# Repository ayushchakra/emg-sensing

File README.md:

# EMG Sensing Circuit Board

Electromygraphy is a medical tool used to evaluate the health of individual muscles and
the nerve cells that dictate their movement. The intention of this project was to design a
four-channel surface electromygraphy (sEMG) printed circuit board in order to process
real-time electromyographic signals generated from a user’s muscle movements. The
board was intended to communicate with a user’s computer via Bluetooth and Serial
to provide flexibility to the physical setup, along with portability for ease of access to
EMG information. The full hardware and software overview can be found [here](https://github.com/ayushchakra/emg-sensing/blob/main/EMG_sensing_final.pdf).

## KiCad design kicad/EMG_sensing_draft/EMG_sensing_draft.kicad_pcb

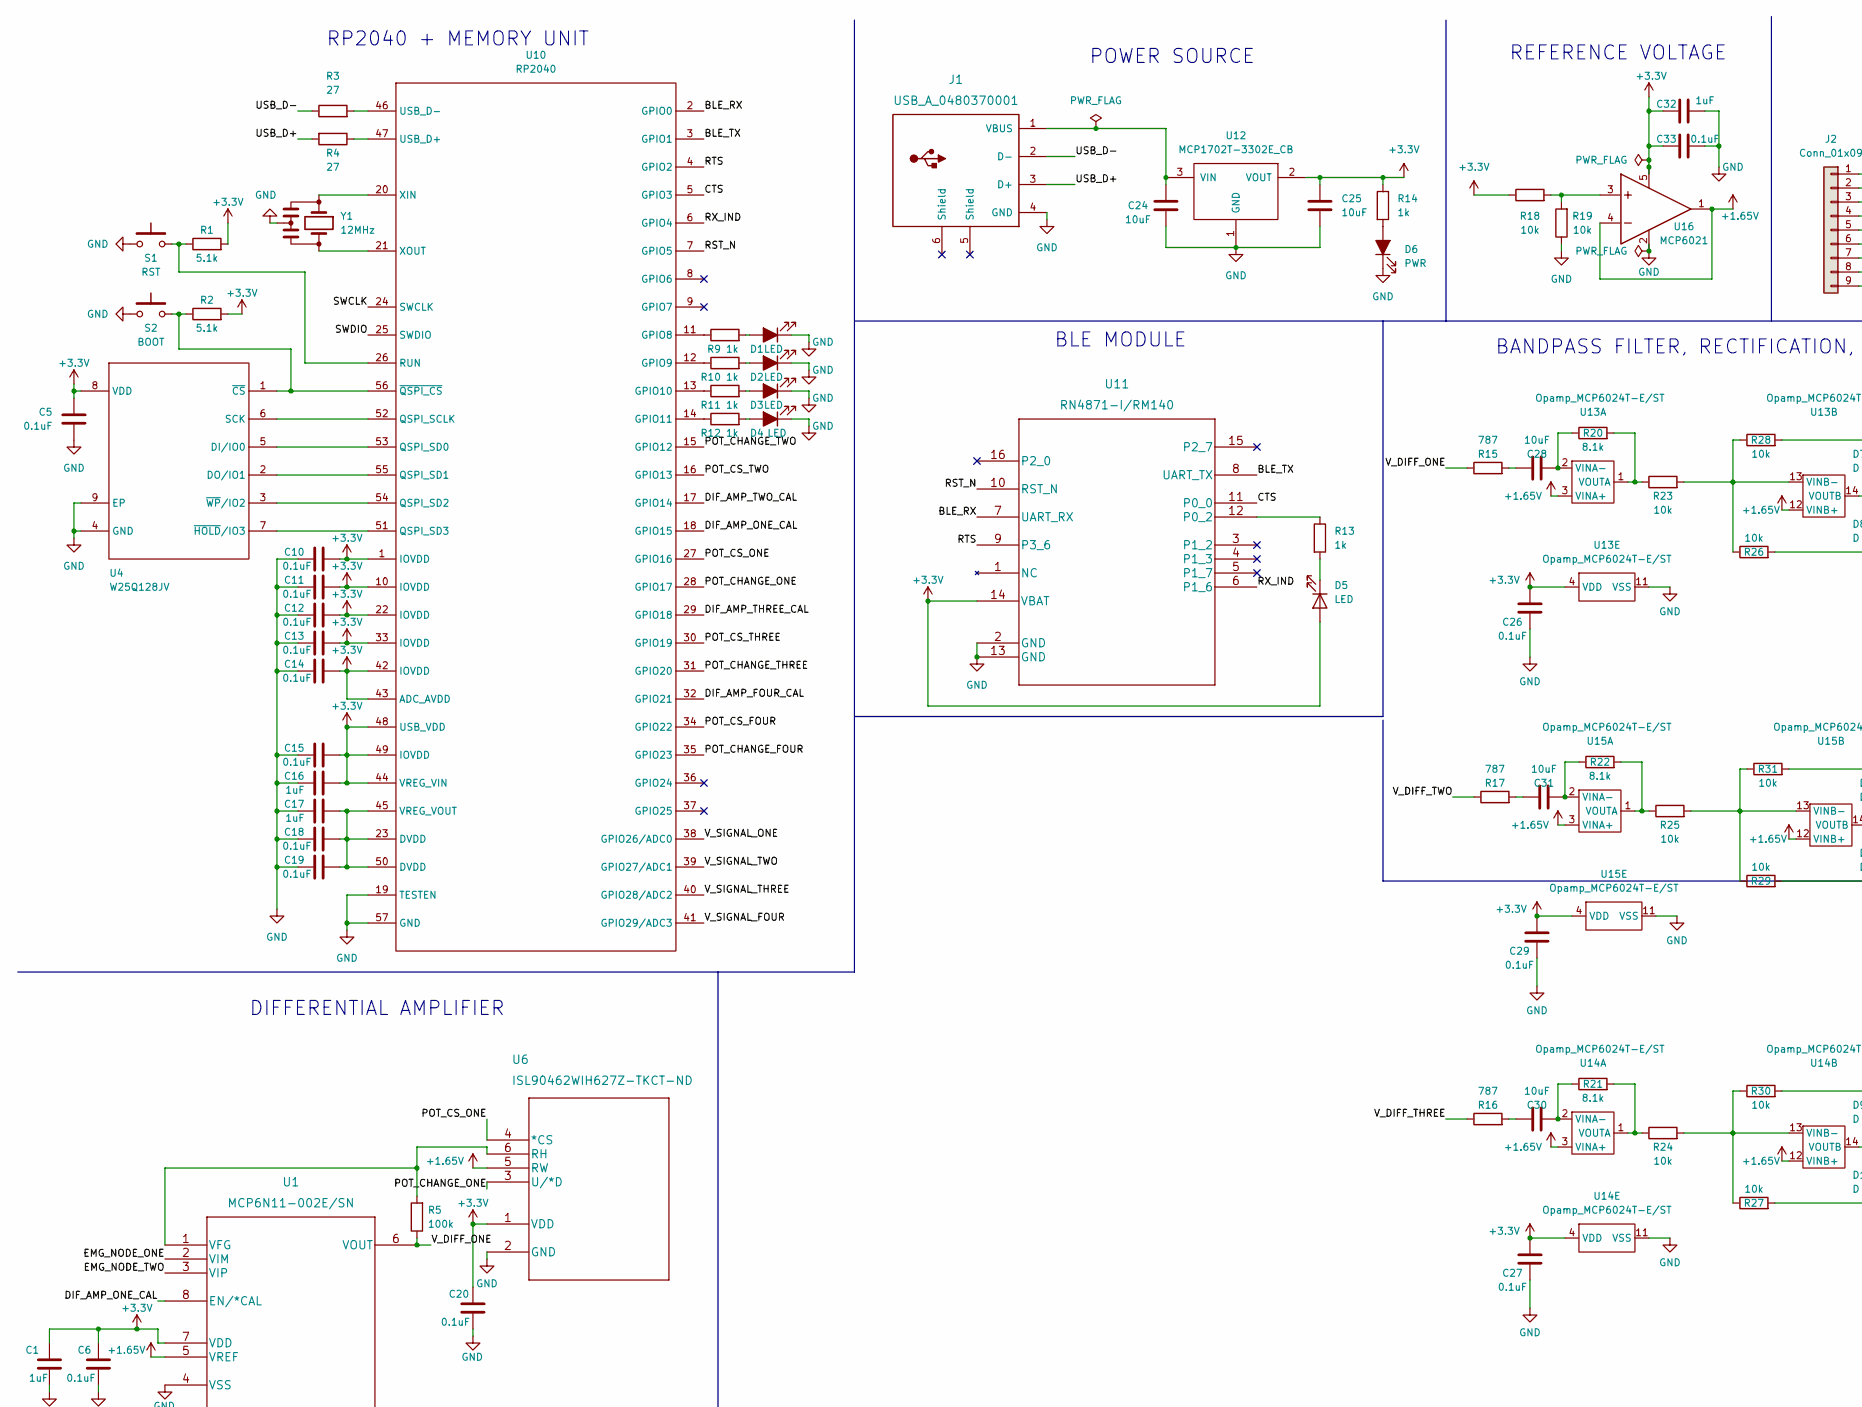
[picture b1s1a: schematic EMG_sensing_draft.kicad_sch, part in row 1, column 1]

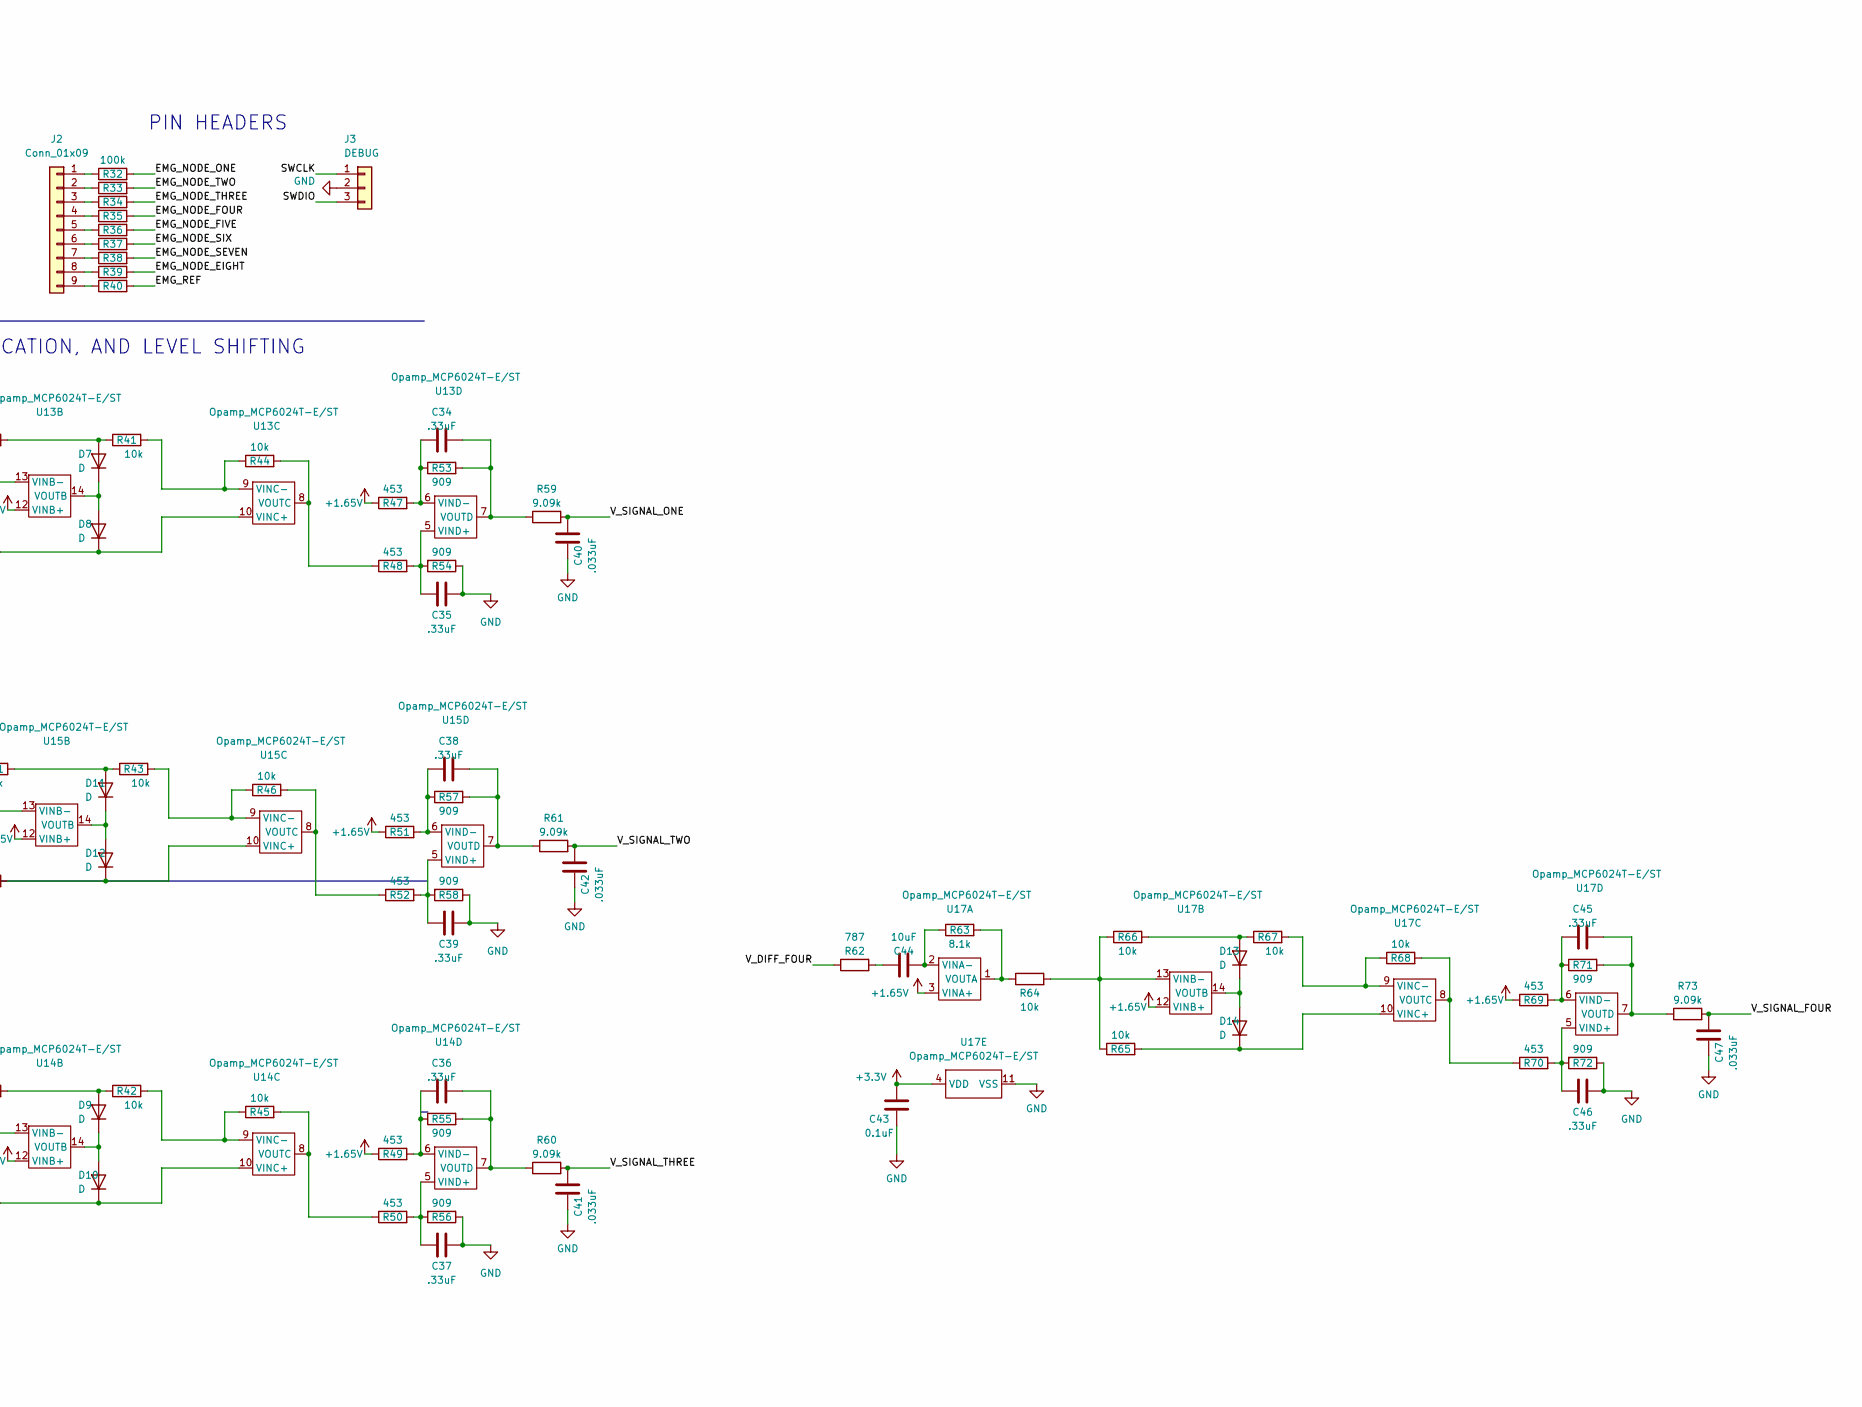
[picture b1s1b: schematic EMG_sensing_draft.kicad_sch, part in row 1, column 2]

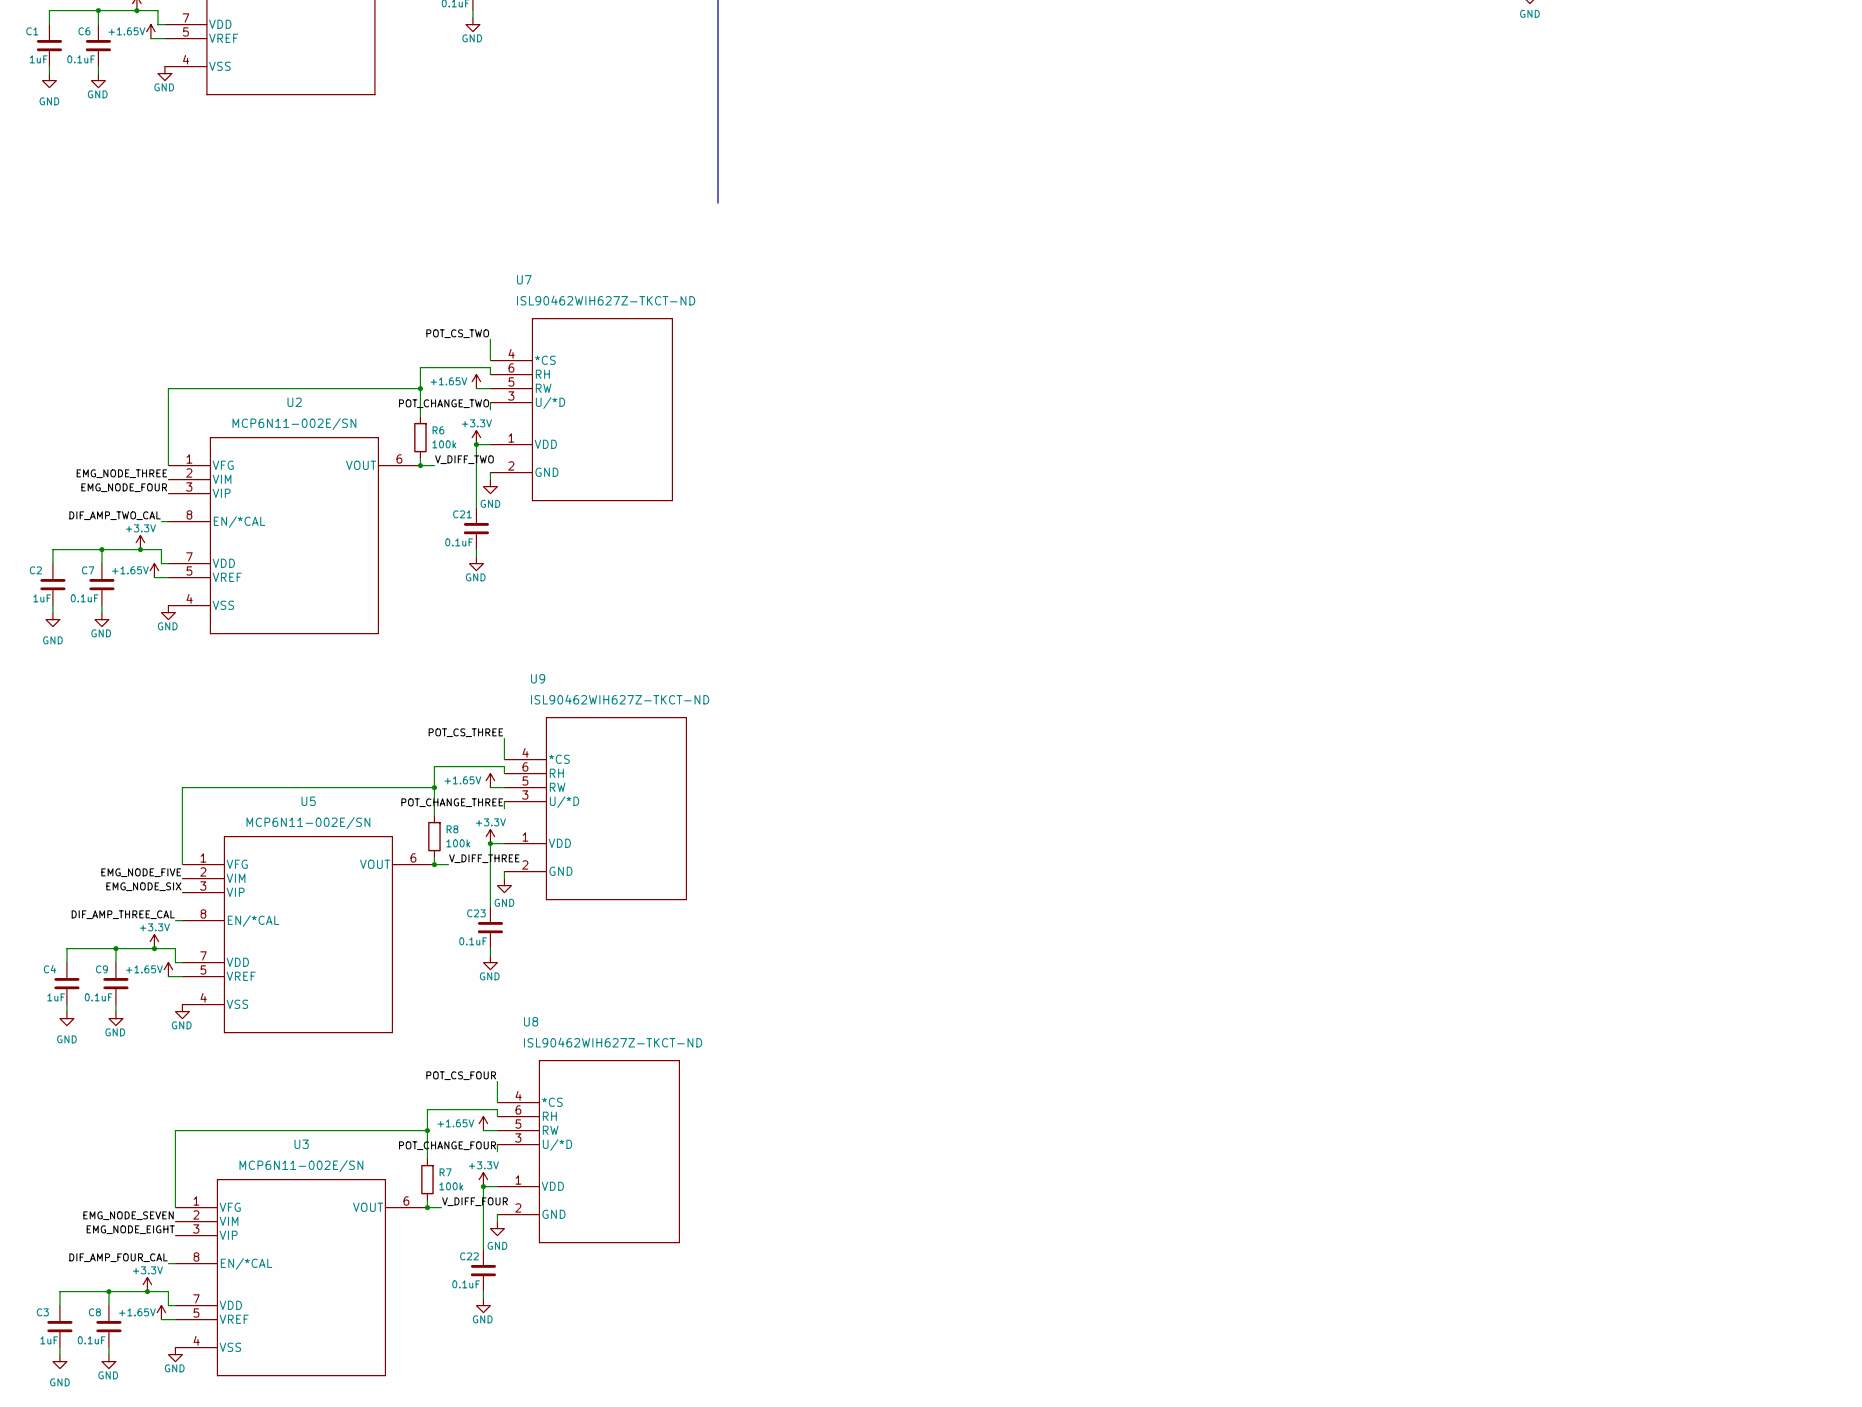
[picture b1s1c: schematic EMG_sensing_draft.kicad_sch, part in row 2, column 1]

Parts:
C1, C2, C3, C4, C16, C17, C32: 1uF; C_0603_1608Metric
C5, C6, C7, C8, C9, C10, C11, C12, C13, C14, C15, C18, C19, C20, C21, C22, C23, C26, C27, C29, C33, C43: 0.1uF; C_0603_1608Metric
C24, C25, C28, C30, C31, C44: 10uF; C_0603_1608Metric
C34, C35, C36, C37, C38, C39, C45, C46: .33uF; C_0603_1608Metric
C40, C41, C42, C47: .033uF; C_0603_1608Metric
D1, D2, D3, D4, D5: LED; LED_0805_2012Metric
D6: PWR; LED_0805_2012Metric
D7, D8, D9, D10, D11, D12, D13, D14: D; D_0805_2012Metric
J1: USB_A_0480370001
J2: Conn_01x09; PinSocket_1x09_P2.54mm_Vertical
J3: DEBUG; PinHeader_1x03_P2.54mm_Vertical
R1, R2: 5.1k; R_0603_1608Metric
R3, R4: 27; R_0603_1608Metric
R5, R6, R7, R8, R32, R33, R34, R35, R36, R37, R38, R39, R40: 100k; R_0603_1608Metric
R9, R10, R11, R12, R13, R14: 1k; R_0603_1608Metric
R15, R16, R17, R62: 787; R_0603_1608Metric
R18, R19, R23, R24, R25, R26, R27, R28, R29, R30, R31, R41, R42, R43, R44, R45, R46, R64, R65, R66, R67, R68: 10k; R_0603_1608Metric
R20, R21, R22, R63: 8.1k; R_0603_1608Metric
R47, R48, R49, R50, R51, R52, R69, R70: 453; R_0603_1608Metric
R53, R54, R55, R56, R57, R58, R71, R72: 909; R_0603_1608Metric
R59, R60, R61, R73: 9.09k; R_0603_1608Metric
S1: RST; TL3301AFxxxxJ
S2: BOOT; TL3301AFxxxxJ
U1, U2, U3, U5: MCP6N11-002E/SN; MCP6N11-002ESN
U4: W25Q128JV; WSON-8-1EP_6x5mm_P1.27mm_EP3.4x4.3mm
U6, U7, U8, U9: ISL90462WIH627Z-TKCT-ND
U10: RP2040
U11: RN4871-I/RM140; RN4871
U12: MCP1702T-3302E_CB; SOT-23
U13, U14, U15, U17: Opamp_MCP6024T-E/ST; MCP6024T
U16: MCP6021; SOT-23-5
Y1: 12MHz; CSTNE

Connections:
+1.65V: R47.1, R49.1, R51.1, R69.1, U1.5 (VREF), U2.5 (VREF), U3.5 (VREF), U5.5 (VREF), U6.5 (RW), U7.5 (RW), U8.5 (RW), U9.5 (RW), U13.3 (VINA+), U13.12 (VINB+), U14.3 (VINA+), U14.12 (VINB+), U15.3 (VINA+), U15.12 (VINB+), U16.1, U16.4, U17.3 (VINA+), U17.12 (VINB+)
+3.3V: C1.1, C2.1, C3.1, C4.1, C5.2, C6.1, C7.1, C8.1, C9.1, C10.1, C11.1, C12.1, C13.1, C14.1, C15.1, C16.1, C20.1, C21.1, C22.1, C23.1, C25.1, C26.2, C27.2, C29.2, C32.1, C33.1, C43.2, D5.2 (A), R1.2, R2.2, R14.1, R18.1, U1.7 (VDD), U2.7 (VDD), U3.7 (VDD), U4.8 (VDD), U5.7 (VDD), U6.1 (VDD), U7.1 (VDD), U8.1 (VDD), U9.1 (VDD), U10.1 (IOVDD), U10.10 (IOVDD), U10.22 (IOVDD), U10.33 (IOVDD), U10.42 (IOVDD), U10.43 (ADC_AVDD), U10.44 (VREG_VIN), U10.48 (USB_VDD), U10.49 (IOVDD), U11.14 (VBAT), U12.2 (VOUT), U13.4 (VDD), U14.4 (VDD), U15.4 (VDD), U16.5, U17.4 (VDD)
/BLE_RX: U10.2 (GPIO0), U11.7 (UART_RX)
/BLE_TX: U10.3 (GPIO1), U11.8 (UART_TX)
/CTS: U10.5 (GPIO3), U11.11 (P0_0)
/DIF_AMP_ONE_CAL: U1.8 (EN/*CAL), U10.18 (GPIO15)
/DIF_AMP_THREE_CAL: U5.8 (EN/*CAL), U10.29 (GPIO18)
/DIF_AMP_TWO_CAL: U2.8 (EN/*CAL), U10.17 (GPIO14)
/EMG_NODE_EIGHT: R39.2, U3.3 (VIP)
/EMG_NODE_FIVE: R36.2, U5.2 (VIM)
/EMG_NODE_FOUR: R35.2, U2.3 (VIP)
/EMG_NODE_ONE: R32.2, U1.2 (VIM)
/EMG_NODE_SEVEN: R38.2, U3.2 (VIM)
/EMG_NODE_SIX: R37.2, U5.3 (VIP)
/EMG_NODE_THREE: R34.2, U2.2 (VIM)
/EMG_NODE_TWO: R33.2, U1.3 (VIP)
/EMG_REF: R40.2
/POT_CHANGE_ONE: U6.3 (U/*D), U10.28 (GPIO17)
/POT_CHANGE_THREE: U9.3 (U/*D), U10.31 (GPIO20)
/POT_CHANGE_TWO: U7.3 (U/*D), U10.15 (GPIO12)
/POT_CS_FOUR: U8.4 (*CS), U10.34 (GPIO22), U10.36 (GPIO24)
/POT_CS_ONE: U6.4 (*CS), U10.27 (GPIO16)
/POT_CS_THREE: U9.4 (*CS), U10.30 (GPIO19)
/POT_CS_TWO: U7.4 (*CS), U10.16 (GPIO13)
/RST_N: U10.7 (GPIO5), U11.10 (RST_N)
/RTS: U10.4 (GPIO2), U11.9 (P3_6)
/RX_IND: U10.6 (GPIO4), U11.6 (P1_6)
/SWCLK: J3.1, U10.24 (SWCLK)
/SWDIO: J3.3, U10.25 (SWDIO)
/USB_D+: J1.3 (D+), R4.2
/USB_D-: J1.2 (D-), R3.1
/V_DIFF_FOUR: R7.1, R62.1, U3.6 (VOUT)
/V_DIFF_ONE: R5.1, R15.1, U1.6 (VOUT)
/V_DIFF_THREE: R8.1, R16.1, U5.6 (VOUT)
/V_DIFF_TWO: R6.1, R17.1, U2.6 (VOUT)
/V_SIGNAL_FOUR: C47.1, R73.2, U10.41 (GPIO29/ADC3)
/V_SIGNAL_ONE: C40.1, R59.2, U10.38 (GPIO26/ADC0)
/V_SIGNAL_THREE: C41.1, R60.2, U10.40 (GPIO28/ADC2)
/V_SIGNAL_TWO: C42.1, R61.2, U10.39 (GPIO27/ADC1)
GND: C1.2, C2.2, C3.2, C4.2, C5.1, C6.2, C7.2, C8.2, C9.2, C10.2, C11.2, C12.2, C13.2, C14.2, C15.2, C16.2, C17.2, C18.2, C19.2, C20.2, C21.2, C22.2, C23.2, C24.1, C25.2, C26.1, C27.1, C29.1, C32.2, C33.2, C35.1, C37.1, C39.1, C40.2, C41.2, C42.2, C43.1, C46.1, C47.2, D1.1 (K), D2.1 (K), D3.1 (K), D4.1 (K), D6.1 (K), J1.4 (GND), J3.2, R19.1, R54.1, R56.1, R58.1, R72.1, S1.1, S2.1, U1.4 (VSS), U2.4 (VSS), U3.4 (VSS), U4.4 (GND), U4.9 (EP), U5.4 (VSS), U6.2 (GND), U7.2 (GND), U8.2 (GND), U9.2 (GND), U10.19 (TESTEN), U10.57 (GND), U11.2 (GND), U11.13 (GND), U12.1 (GND), U13.11 (VSS), U14.11 (VSS), U15.11 (VSS), U16.2, U17.11 (VSS), Y1.2
unnamed: C17.1, C18.1, C19.1, U10.23 (DVDD), U10.45 (VREG_VOUT), U10.50 (DVDD)
unnamed: C24.2, J1.1 (VBUS), U12.3 (VIN)
unnamed: C28.1, R15.2
unnamed: C28.2, R20.1, U13.2 (VINA-)
unnamed: C30.1, R16.2
unnamed: C30.2, R21.1, U14.2 (VINA-)
unnamed: C31.1, R17.2
unnamed: C31.2, R22.1, U15.2 (VINA-)
unnamed: C34.1, R47.2, R53.1, U13.6 (VIND-)
unnamed: C34.2, R53.2, R59.1, U13.7 (VOUTD)
unnamed: C35.2, R48.2, R54.2, U13.5 (VIND+)
unnamed: C36.1, R49.2, R55.1, U14.6 (VIND-)
unnamed: C36.2, R55.2, R60.1, U14.7 (VOUTD)
unnamed: C37.2, R50.2, R56.2, U14.5 (VIND+)
unnamed: C38.1, R51.2, R57.1, U15.6 (VIND-)
unnamed: C38.2, R57.2, R61.1, U15.7 (VOUTD)
unnamed: C39.2, R52.2, R58.2, U15.5 (VIND+)
unnamed: C44.1, R62.2
unnamed: C44.2, R63.1, U17.2 (VINA-)
unnamed: C45.1, R69.2, R71.1, U17.6 (VIND-)
unnamed: C45.2, R71.2, R73.1, U17.7 (VOUTD)
unnamed: C46.2, R70.2, R72.2, U17.5 (VIND+)
unnamed: D1.2 (A), R9.2
unnamed: D2.2 (A), R10.2
unnamed: D3.2 (A), R11.2
unnamed: D4.2 (A), R12.2
unnamed: D5.1 (K), R13.2
unnamed: D6.2 (A), R14.2
unnamed: D7.1 (K), D8.2 (A), U13.14 (VOUTB)
unnamed: D7.2 (A), R28.2, R41.1
unnamed: D8.1 (K), R26.2, U13.10 (VINC+)
unnamed: D9.2 (A), R30.2, R42.1
unnamed: D10.1 (K), R27.2, U14.10 (VINC+)
unnamed: D9.1 (K), D10.2 (A), U14.14 (VOUTB)
unnamed: D11.1 (K), D12.2 (A), U15.14 (VOUTB)
unnamed: D11.2 (A), R31.2, R43.1
unnamed: D12.1 (K), R29.2, U15.10 (VINC+)
unnamed: D13.1 (K), D14.2 (A), U17.14 (VOUTB)
unnamed: D13.2 (A), R66.2, R67.1
unnamed: D14.1 (K), R65.2, U17.10 (VINC+)
unnamed: J2.1, R32.1
unnamed: J2.2, R33.1
unnamed: J2.3, R34.1
unnamed: J2.4, R35.1
unnamed: J2.5, R36.1
unnamed: J2.6, R37.1
unnamed: J2.7, R38.1
unnamed: J2.8, R39.1
unnamed: J2.9, R40.1
unnamed: R1.1, S1.2, U10.26 (RUN)
unnamed: R2.1, S2.2, U4.1 (~CS), U10.56 (~QSPI_CS)
unnamed: R3.2, U10.46 (USB_D-)
unnamed: R4.1, U10.47 (USB_D+)
unnamed: R5.2, U1.1 (VFG), U6.6 (RH)
unnamed: R6.2, U2.1 (VFG), U7.6 (RH)
unnamed: R7.2, U3.1 (VFG), U8.6 (RH)
unnamed: R8.2, U5.1 (VFG), U9.6 (RH)
unnamed: R9.1, U10.11 (GPIO8)
unnamed: R10.1, U10.12 (GPIO9)
unnamed: R11.1, U10.13 (GPIO10)
unnamed: R12.1, U10.14 (GPIO11)
unnamed: R13.1, U11.12 (P0_2)
unnamed: R18.2, R19.2, U16.3
unnamed: R20.2, R23.1, U13.1 (VOUTA)
unnamed: R21.2, R24.1, U14.1 (VOUTA)
unnamed: R22.2, R25.1, U15.1 (VOUTA)
unnamed: R23.2, R26.1, R28.1, U13.13 (VINB-)
unnamed: R24.2, R27.1, R30.1, U14.13 (VINB-)
unnamed: R25.2, R29.1, R31.1, U15.13 (VINB-)
unnamed: R41.2, R44.1, U13.9 (VINC-)
unnamed: R42.2, R45.1, U14.9 (VINC-)
unnamed: R43.2, R46.1, U15.9 (VINC-)
unnamed: R44.2, R48.1, U13.8 (VOUTC)
unnamed: R45.2, R50.1, U14.8 (VOUTC)
unnamed: R46.2, R52.1, U15.8 (VOUTC)
unnamed: R63.2, R64.1, U17.1 (VOUTA)
unnamed: R64.2, R65.1, R66.1, U17.13 (VINB-)
unnamed: R67.2, R68.1, U17.9 (VINC-)
unnamed: R68.2, R70.1, U17.8 (VOUTC)
unnamed: U10.20 (XIN), Y1.1
unnamed: U10.21 (XOUT), Y1.3
unnamed: U4.7 (~HOLD/IO3), U10.51 (QSPI_SD3)
unnamed: U4.6 (SCK), U10.52 (QSPI_SCLK)
unnamed: U4.5 (DI/IO0), U10.53 (QSPI_SD0)
unnamed: U4.3 (~WP/IO2), U10.54 (QSPI_SD2)
unnamed: U4.2 (DO/IO1), U10.55 (QSPI_SD1)

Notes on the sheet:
BLE MODULE
DIFFERENTIAL AMPLIFIER
BANDPASS FILTER, RECTIFICATION, AND LEVEL SHIFTING
PIN HEADERS
REFERENCE VOLTAGE
POWER SOURCE
RP2040 + MEMORY UNIT

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
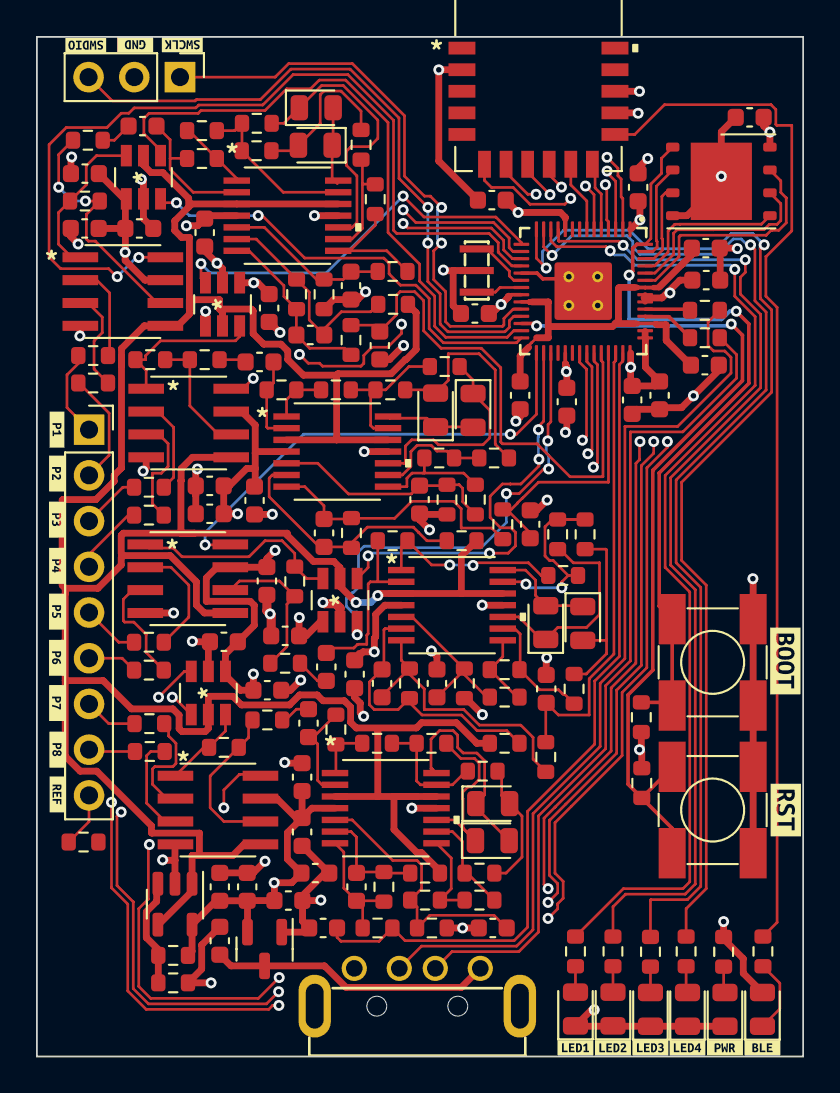
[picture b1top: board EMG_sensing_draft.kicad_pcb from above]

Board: 4 copper layers, 42.6 x 56.6 mm, 177 parts (0 on the bottom side), 127 nets.

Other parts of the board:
kibuzzard-63775D6F: G***; kibuzzard-63775D6F
kibuzzard-63775D95: G***; kibuzzard-63775D95
kibuzzard-63775DA9: G***; kibuzzard-63775DA9
kibuzzard-63775DCC: G***; kibuzzard-63775DCC
kibuzzard-63775DF3: G***; kibuzzard-63775DF3
kibuzzard-63775E2B: G***; kibuzzard-63775E2B
kibuzzard-63775E08: G***; kibuzzard-63775E08
kibuzzard-63775E55: G***; kibuzzard-63775E55
kibuzzard-63775E69: G***; kibuzzard-63775E69
kibuzzard-63775E81: G***; kibuzzard-63775E81
kibuzzard-63775ECF: G***; kibuzzard-63775ECF
kibuzzard-63775F9D: G***; kibuzzard-63775F9D
kibuzzard-63775F11: G***; kibuzzard-63775F11
kibuzzard-63775F30: G***; kibuzzard-63775F30
kibuzzard-63775F41: G***; kibuzzard-63775F41
kibuzzard-63775F53: G***; kibuzzard-63775F53
kibuzzard-63775FC8: G***; kibuzzard-63775FC8
kibuzzard-63775FF7: G***; kibuzzard-63775FF7
kibuzzard-6377605B: G***; kibuzzard-6377605B
kibuzzard-63776016: G***; kibuzzard-63776016

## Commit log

2022-10-25 Add kicad schematics draft
2022-10-25 Add parts folder and components
2022-10-25 added Eclectronics folder
2022-10-25 added gitignore
2022-10-25 updated file path
2022-10-27 added autosaved files to gitignore
2022-10-27 restructured parts library
2022-10-27 added inamp
2022-10-27 Add rp2040 to schematics
2022-10-27 added BLE module and cleaned up schematic
2022-10-28 Add R and C values (please check!)
2022-10-28 updated RC filter characteristic freq
2022-10-28 Updated resistor values
2022-10-28 added notes from dr1
2022-10-28 Update after design review
2022-11-01 Update circuit based on Brad's advice
2022-11-01 added change list
2022-11-01 Change opamp chip and add bypass
2022-11-01 Fix diode
2022-11-01 Update circuit w new resistor values
2022-11-02 added power symbol and cleaned up schematic
2022-11-02 added level shifter and second order low pass filter
2022-11-02 added simulation for level shifter
2022-11-02 restructured repo
2022-11-02 fixed mcp6024 schematic symbol
2022-11-04 added digital potentiometer
2022-11-05 Create circuit sims
2022-11-05 Update rectifying circuit
2022-11-06 linked schematic symbols to footprints
2022-11-06 added rectification simulation
2022-11-06 fixed rectifier schematic
2022-11-06 added full schematic simulation (without diff amp)
2022-11-07 added ltspice model for mcp6n11 to filter sim
2022-11-07 Add diff amp simulation (incomplete)
2022-11-07 added txt to generate mcp6n11 spice model
2022-11-08 Change schematics based on Brad's comments (incomplete)
2022-11-08 fixed ble pin connection
2022-11-08 Add Brad suggestions
2022-11-08 Edited multi-unit component
2022-11-09 fixed ble pins
2022-11-11 updated footprint assignments
2022-11-11 added three channels for emg sensing
2022-11-11 adde reformmated filtering symbol
2022-11-11 cleaned up four channel schematic
2022-11-11 Add two channel schematics
2022-11-11 organized parts on layout
2022-11-14 placed filtering components
2022-11-14 started routing power lines
2022-11-15 finished initial layout
2022-11-15 Fix errors in layout
2022-11-15 Fix layout issues
2022-11-16 removed references from silkscreen
2022-11-17 fixed rn4871 position
2022-11-17 added two layers to board
2022-11-17 fixed rn4871 ground fill
2022-11-17 fixed overlapping courtyards
2022-11-18 fixed copper fill
2022-11-18 removed references
2022-11-18 finished four layer layout
2022-11-18 added silkscreen labels and fixed drc issues
2022-11-18 fixed usb mounting
2022-11-18 cleaned directory
2022-11-18 Revert "Developed 4-Layer Layout for EMG Sensing Board"
2022-12-02 adding ibom
2022-12-15 added firmware and software for emg sensing
2022-12-18 --wip-- [skip ci]
2022-12-18 added heirarichal sheets
2022-12-18 changed main schematic to reference heirarichal sheets
2022-12-18 organized repo
2022-12-19 removing temp file
2022-12-19 updated gain
2022-12-27 added report

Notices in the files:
parts and their libraries:
Copyright 2021 Accelerated Designs. All rights reserved.
